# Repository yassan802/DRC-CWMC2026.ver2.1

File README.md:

ESP32を搭載しており、Bluetoothでの通信が可能な中央制御基板。他の基板と通信する用とロボマス等と通信する用の２つのCAN系統がある。外部からの信号で動かせるMD基板用の端子もある。基板に挿した状態だとesp32にファームウェアを書き込めないことやLCDのコントラスト調整ができなかったりといくつかの欠陥を抱えているのですでにあるものを見ながらパターンカット、違法建築を行うことを推奨する。  
そのほかの欠点としてはピンヘッダを用いてESP32とLCDを付けることを想定しているので分厚くなることがある。

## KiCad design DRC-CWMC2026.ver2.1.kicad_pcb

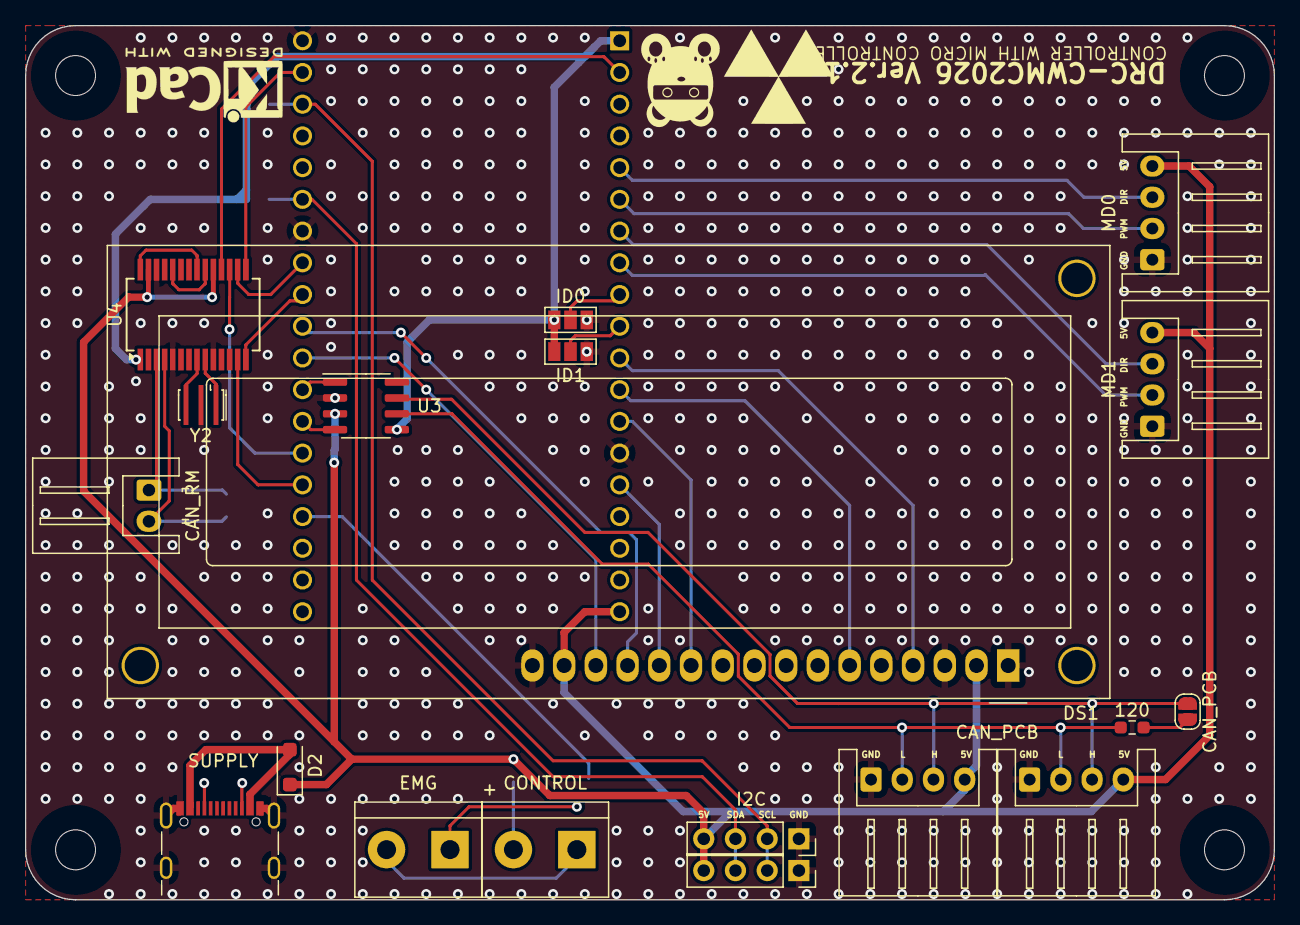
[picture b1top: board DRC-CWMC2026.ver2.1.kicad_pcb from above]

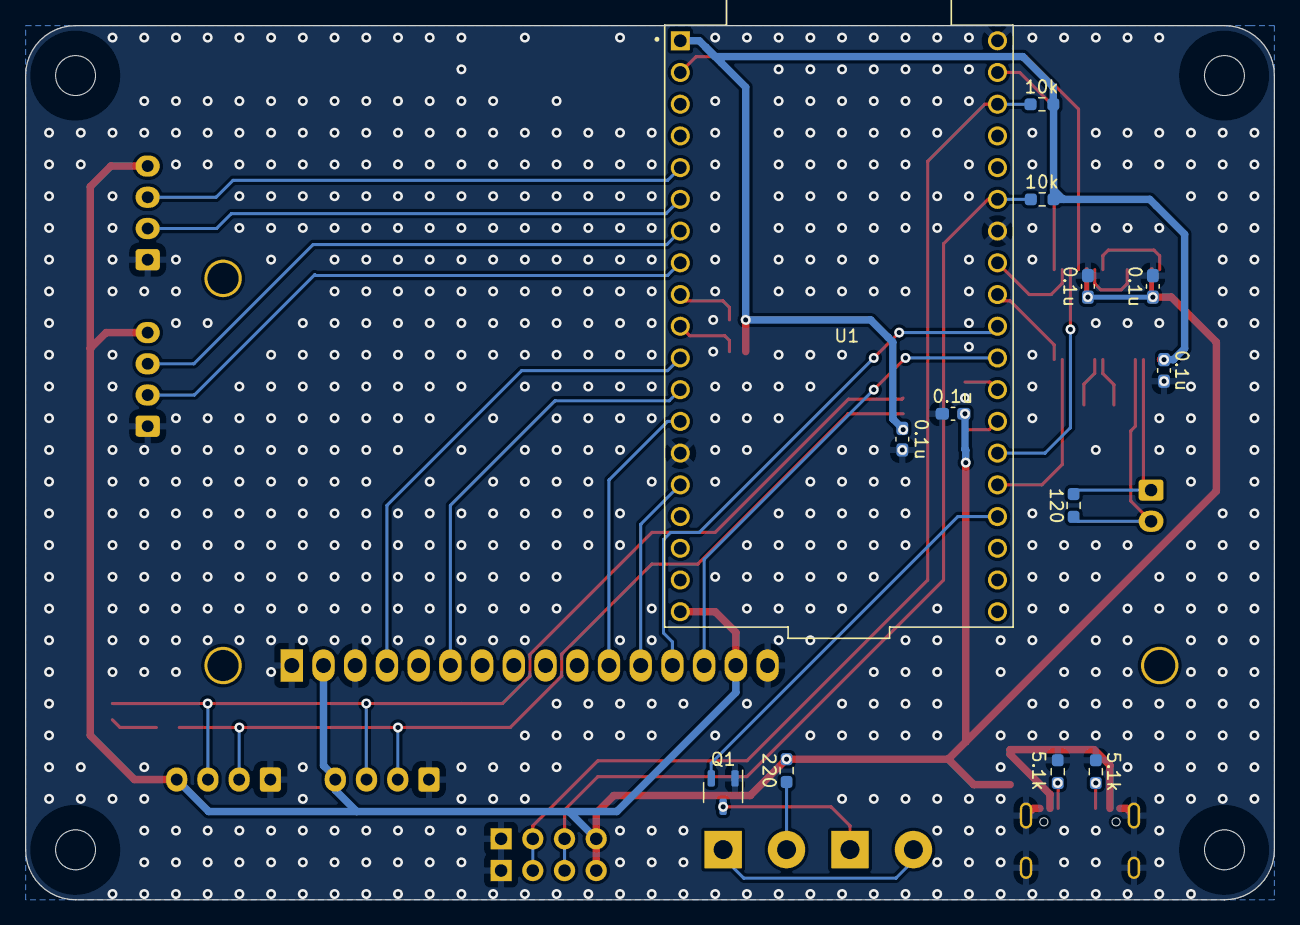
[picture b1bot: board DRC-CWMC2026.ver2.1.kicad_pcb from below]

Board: 2 copper layers, 100.0 x 70.0 mm, 32 parts (13 on the bottom side), 41 nets.

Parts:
0.1u, 0.1u#2, 0.1u#5: 0.1μ; C_0603_1608Metric_Pad1.08x0.95mm_HandSolder
0.1u#3, 0.1u#4: 0.1u; C_0603_1608Metric_Pad1.08x0.95mm_HandSolder
5.1k, 5.1k#2: 5.1k; R_0603_1608Metric_Pad0.98x0.95mm_HandSolder
10k, 10k#2: 10k; R_0603_1608Metric_Pad0.98x0.95mm_HandSolder
120, 120#2: 120; R_0603_1608Metric_Pad0.98x0.95mm_HandSolder
220: 220; R_0603_1608Metric_Pad0.98x0.95mm_HandSolder
CAN_PCB: CAN_RM; SolderJumper-2_P1.3mm_Open_RoundedPad1.0x1.5mm
CAN_RM: Conn_01x02_Pin; JST_XH_S2B-XH-A_1x02_P2.50mm_Horizontal
D2: ss2040; D_SOD-123F
DS1: WC1602A
J2, J3: CAN_PCB; JST_XH_S4B-XH-A_1x04_P2.50mm_Horizontal
J4: SUPPLY; USB_C_Receptacle_GCT_USB4105-xx-A_16P_TopMnt_Horizontal
J5, J6: I2C; PinSocket_1x04_P2.54mm_Vertical
J7: CONTROL; TerminalBlock_bornier-2_P5.08mm
J8: EMG; TerminalBlock_bornier-2_P5.08mm
JP1: ID0; SolderJumper-3_P1.3mm_Open_Pad1.0x1.5mm_NumberLabels
JP2: ID1; SolderJumper-3_P1.3mm_Open_Pad1.0x1.5mm_NumberLabels
MD0, MD1: MD; JST_XH_S4B-XH-A_1x04_P2.50mm_Horizontal
Q1: DTC143Z; SOT-23-3
U1: ESP32-DEVKITC; MODULE_ESP32-DEVKITC
U3: MCP2562-H-SN; SOIC-8_3.9x4.9mm_P1.27mm
U4: MCP25625-x-SS; SSOP-28_5.3x10.2mm_P0.65mm
Y2: 16MHz; Resonator_SMD_Murata_CSTxExxV-3Pin_3.0x1.1mm_HandSoldering

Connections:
+3.3V: 0.1u.1, 0.1u#3.2, 10k.1, 10k#2.1, JP1.3 (B), JP2.3 (B), U1.1 (3V3), U3.5 (Vio), U4.1 (VIO)
+5V: 0.1u#2.1, 0.1u#4.2, 0.1u#5.1, 220.1, D2.1 (K), DS1.2 (VDD), DS1.15 (LED(+)), J2.4, J3.4, J5.4, J6.4, MD0.4, MD1.4, U1.19 (EXT_5V), U3.3 (VDD), U4.19 (VDD), U4.27 (VDDA)
CAN_RX: U1.26 (IO4), U3.4 (RXD)
CAN_TX: U1.27 (IO16), U3.1 (TXD)
CONTROL: Q1.2 (B), U1.23 (IO15)
CS_CAN: U1.25 (IO0), U4.17 (~CS)
DIR1: MD0.3, U1.5 (IO34)
DIR2: MD1.3, U1.7 (IO32)
GND: 0.1u.2, 0.1u#2.2, 0.1u#3.1, 0.1u#4.1, 0.1u#5.2, 5.1k.1, 5.1k#2.1, DS1.1 (VSS), DS1.3 (VO), DS1.16 (LED(-)), J2.1, J3.1, J4.A1 (GND), J4.A12 (GND), J4.B1 (GND), J4.B12 (GND), J4.S1 (SHIELD), J5.1, J6.1, JP1.1 (A), JP2.1 (A), MD0.1, MD1.1, Q1.1 (E), U1.14 (GND1), U1.32 (GND2), U1.38 (GND3), U3.2 (VSS), U3.8 (STBY), U4.5 (STBY), U4.10 (GND), U4.26 (VSS), Y2.2
LCD1_D4: DS1.11 (D4), U1.13 (IO12)
LCD1_D5: DS1.12 (D5), U1.15 (IO13)
LCD1_D6: DS1.13 (D6), U1.29 (IO5)
LCD1_D7: DS1.14 (D7), U1.28 (IO17)
LCD_E: DS1.6 (E), U1.12 (IO14)
LCD_RS: DS1.4 (RS), U1.11 (IO27)
MISO: U1.31 (IO19), U4.16 (SO)
MOSI: U1.37 (IO23), U4.15 (SI)
unnamed: D2.2 (A), J4.A4 (VBUS), J4.A9 (VBUS), J4.B4 (VBUS), J4.B9 (VBUS)
unnamed: 5.1k.2, J4.A5 (CC1)
unnamed: 5.1k#2.2, J4.B5 (CC2)
unnamed: J7.1, J8.2
unnamed: 220.2, J7.2
unnamed: J8.1, Q1.3 (C)
unnamed: JP1.2 (C), U1.9 (IO25)
unnamed: JP2.2 (C), U1.10 (IO26)
unnamed: 120.1, CAN_PCB.1 (A)
unnamed: U4.9 (OSC1), Y2.1
unnamed: U4.8 (OSC2), Y2.3
unnamed: U4.21 (RxCAN), U4.28 (RXD)
unnamed: U4.20 (TxCAN), U4.24 (TXD)
PCBCAN_H: CAN_PCB.2 (B), J2.3, J3.3, U3.7 (CANH)
PCBCAN_L: 120.2, J2.2, J3.2, U3.6 (CANL)
PCB_INT: U1.24 (IO2), U4.13 (~INT)
PWM1: MD0.2, U1.6 (IO35)
PWM2: MD1.2, U1.8 (IO33)
RESET: U1.2 (EN), U4.18 (~RESET)
RMCAN_H: 120#2.2, CAN_RM.2, U4.4 (CANH)
RMCAN_L: 120#2.1, CAN_RM.1, U4.3 (CANL)
SCK: U1.30 (IO18), U4.14 (SCK)
SCL: 10k.2, J5.2, J6.2, U1.36 (IO22)
SDA: 10k#2.2, J5.3, J6.3, U1.33 (IO21)
